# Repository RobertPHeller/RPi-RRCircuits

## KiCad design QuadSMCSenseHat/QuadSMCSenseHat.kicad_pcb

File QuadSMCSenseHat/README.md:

# QuadSMCSenseHat

Quad Stall Motor w/ Sense Hat for a Raspberry Pi.

* [Order this board from The Country Robot](https://www.thecountryrobot.com/product/quad-stall-motor-control-and-sense-hat-for-rpi-bare-circuit-board-w-doc/)
* [Order this board from PCBWay](https://www.pcbway.com/project/shareproject/Quad_Stall_Motor_Controller_w__point_Sense__hat_.html)

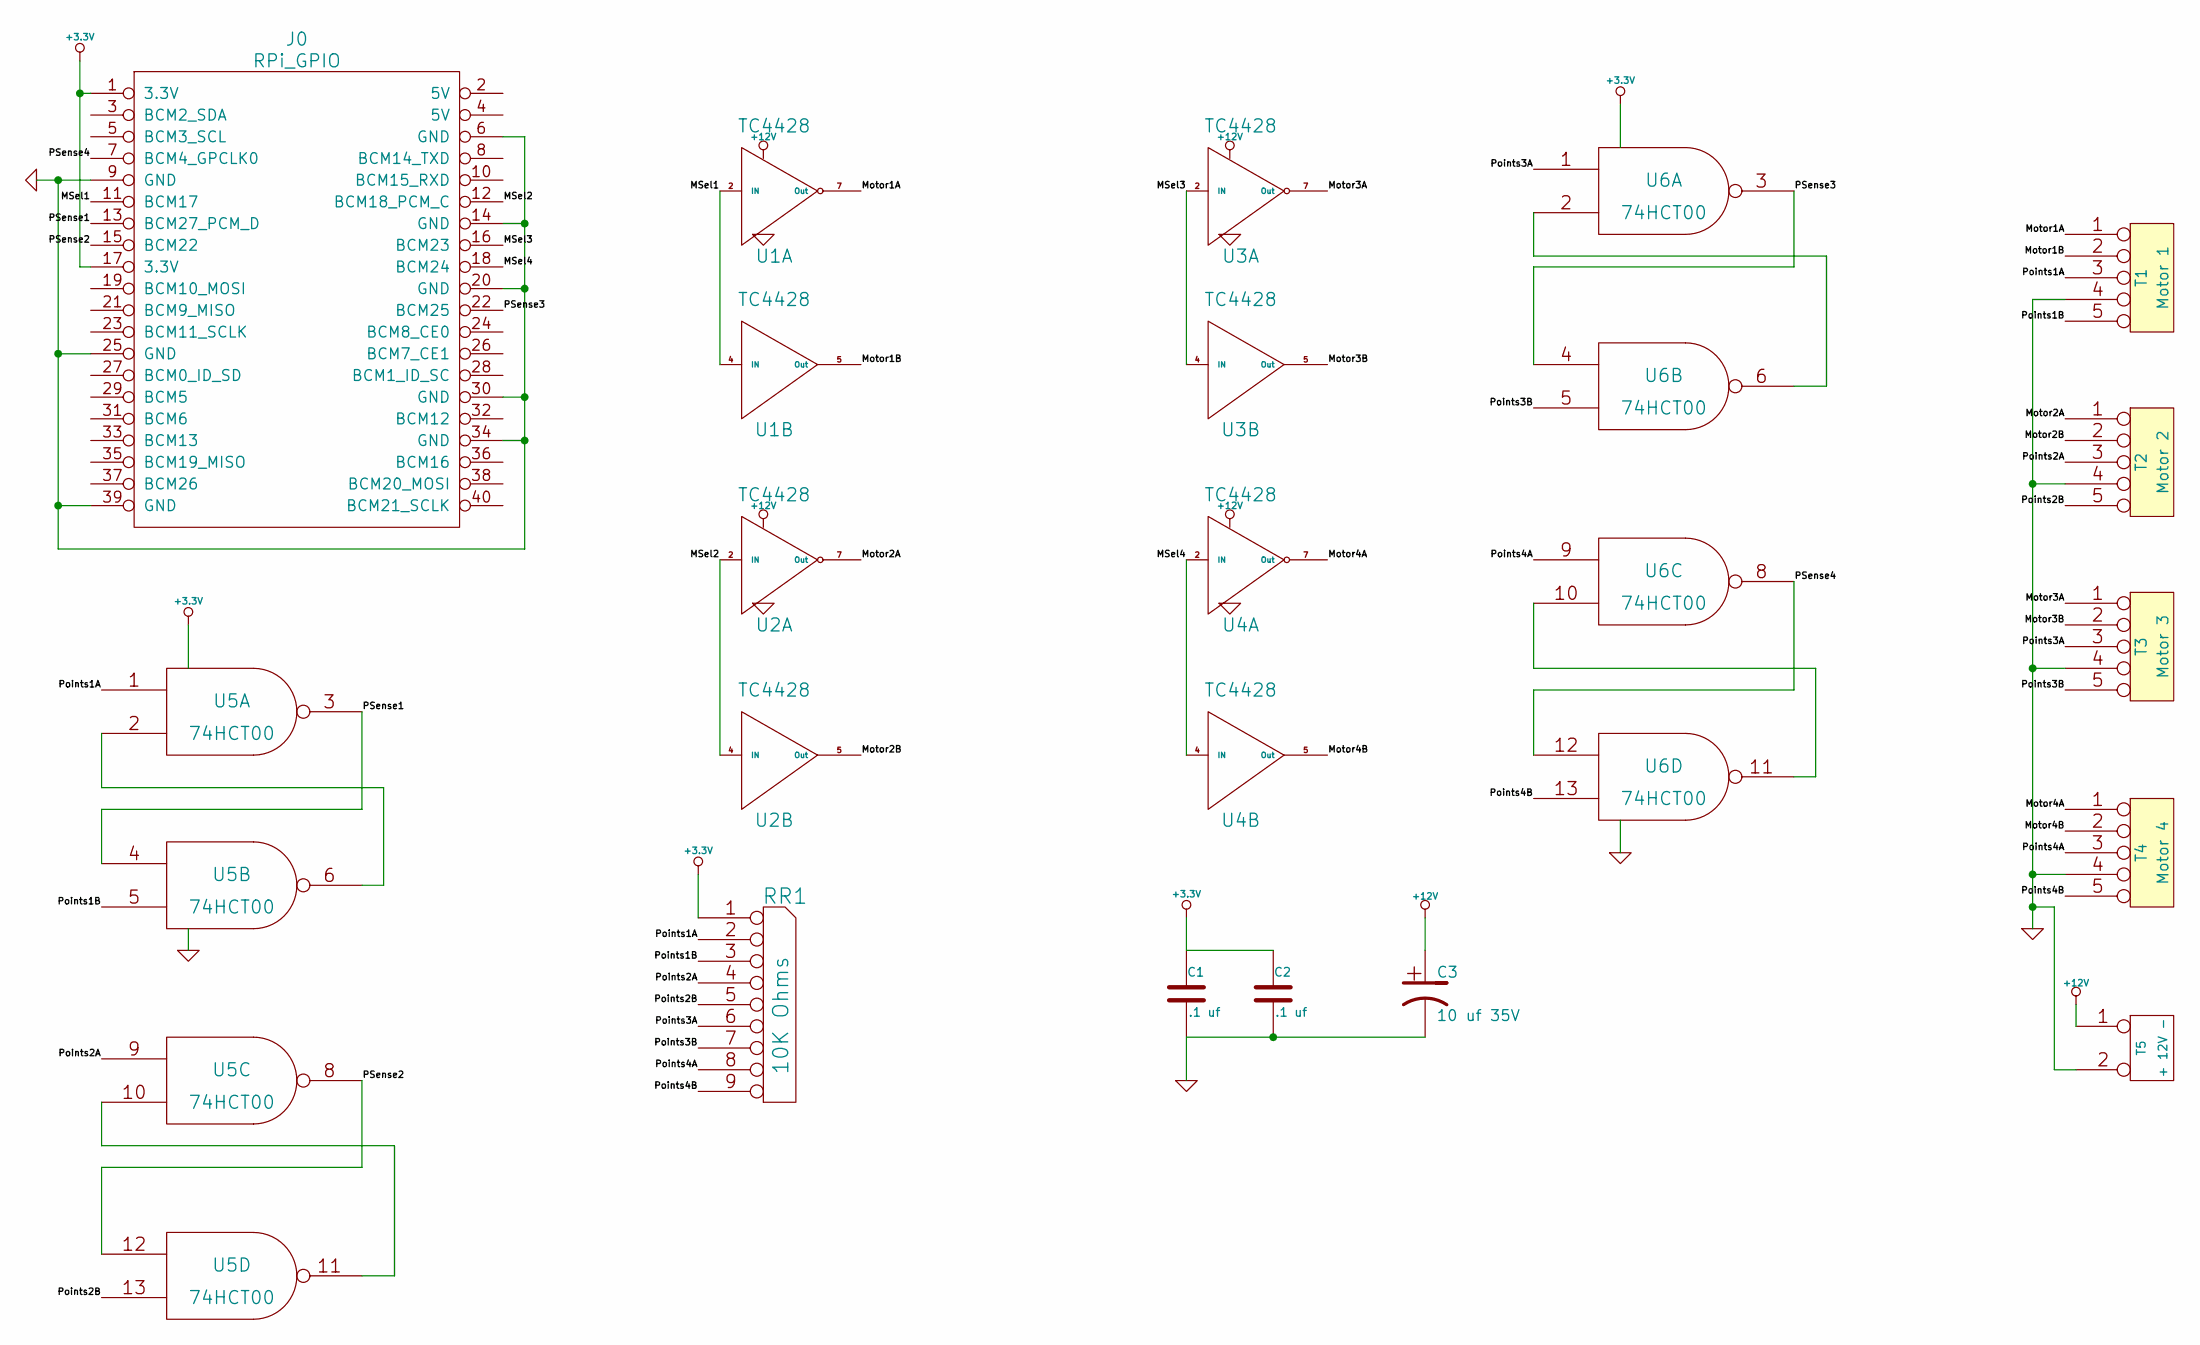
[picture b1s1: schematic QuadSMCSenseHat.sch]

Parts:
C1, C2: .1 uf; Mouser Part Number 581-SR201C104KARTR1
C3: 10 uf 35V; Mouser Part Number 667-ECA-1HM100I
J0: RPi_GPIO; Pin_Header_Straight_2x20; Mouser Part Number 855-M20-6102045
RR1: 10K Ohms; Mouser Part Number 652-4609X-1LF-10K
T1: Motor 1; Mouser Part Number 651-1725685
T2: Motor 2; Mouser Part Number 651-1725685
T3: Motor 3; Mouser Part Number 651-1725685
T4: Motor 4; Mouser Part Number 651-1725685
T5: + 12V -; Mouser Part Number 651-1725656
U1, U2, U3, U4: TC4428; Mouser Part Number 579-TC4428VPA
U5, U6: 74HCT00; Mouser Part Number 595-SN74AHC00N

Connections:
+3.3V: C1.1, C2.1, J0.1 (3.3V), J0.17 (3.3V), RR1.1 (COM), U5.14 (VCC), U6.14 (VCC)
+12V: C3.1, T5.1, U1.6 (Vdd), U2.6 (Vdd), U3.6 (Vdd), U4.6 (Vdd)
/MSel1: J0.11 (BCM17), U1.2 (IN), U1.4 (IN)
/MSel2: J0.12 (BCM18_PCM_C), U2.2 (IN), U2.4 (IN)
/MSel3: J0.16 (BCM23), U3.2 (IN), U3.4 (IN)
/MSel4: J0.18 (BCM24), U4.2 (IN), U4.4 (IN)
/Motor1A: T1.1, U1.7 (Out)
/Motor1B: T1.2, U1.5 (Out)
/Motor2A: T2.1, U2.7 (Out)
/Motor2B: T2.2, U2.5 (Out)
/Motor3A: T3.1, U3.7 (Out)
/Motor3B: T3.2, U3.5 (Out)
/Motor4A: T4.1, U4.7 (Out)
/Motor4B: T4.2, U4.5 (Out)
/PSense1: J0.13 (BCM27_PCM_D), U5.3, U5.4
/PSense2: J0.15 (BCM22), U5.8, U5.12
/PSense3: J0.22 (BCM25), U6.3, U6.4
/PSense4: J0.7 (BCM4_GPCLK0), U6.8, U6.12
/Points1A: RR1.2, T1.3, U5.1
/Points1B: RR1.3, T1.5, U5.5
/Points2A: RR1.4, T2.3, U5.9
/Points2B: RR1.5, T2.5, U5.13
/Points3A: RR1.6, T3.3, U6.1
/Points3B: RR1.7, T3.5, U6.5
/Points4A: RR1.8, T4.3, U6.9
/Points4B: RR1.9, T4.5, U6.13
GND: C1.2, C2.2, C3.2, J0.6 (GND), J0.9 (GND), J0.14 (GND), J0.20 (GND), J0.25 (GND), J0.30 (GND), J0.34 (GND), J0.39 (GND), T1.4, T2.4, T3.4, T4.4, T5.2 (PM), U1.3 (GND), U2.3 (GND), U3.3 (GND), U4.3 (GND), U5.7 (GND), U6.7 (GND)
unnamed: U5.10, U5.11
unnamed: U5.2, U5.6
unnamed: U6.10, U6.11
unnamed: U6.2, U6.6

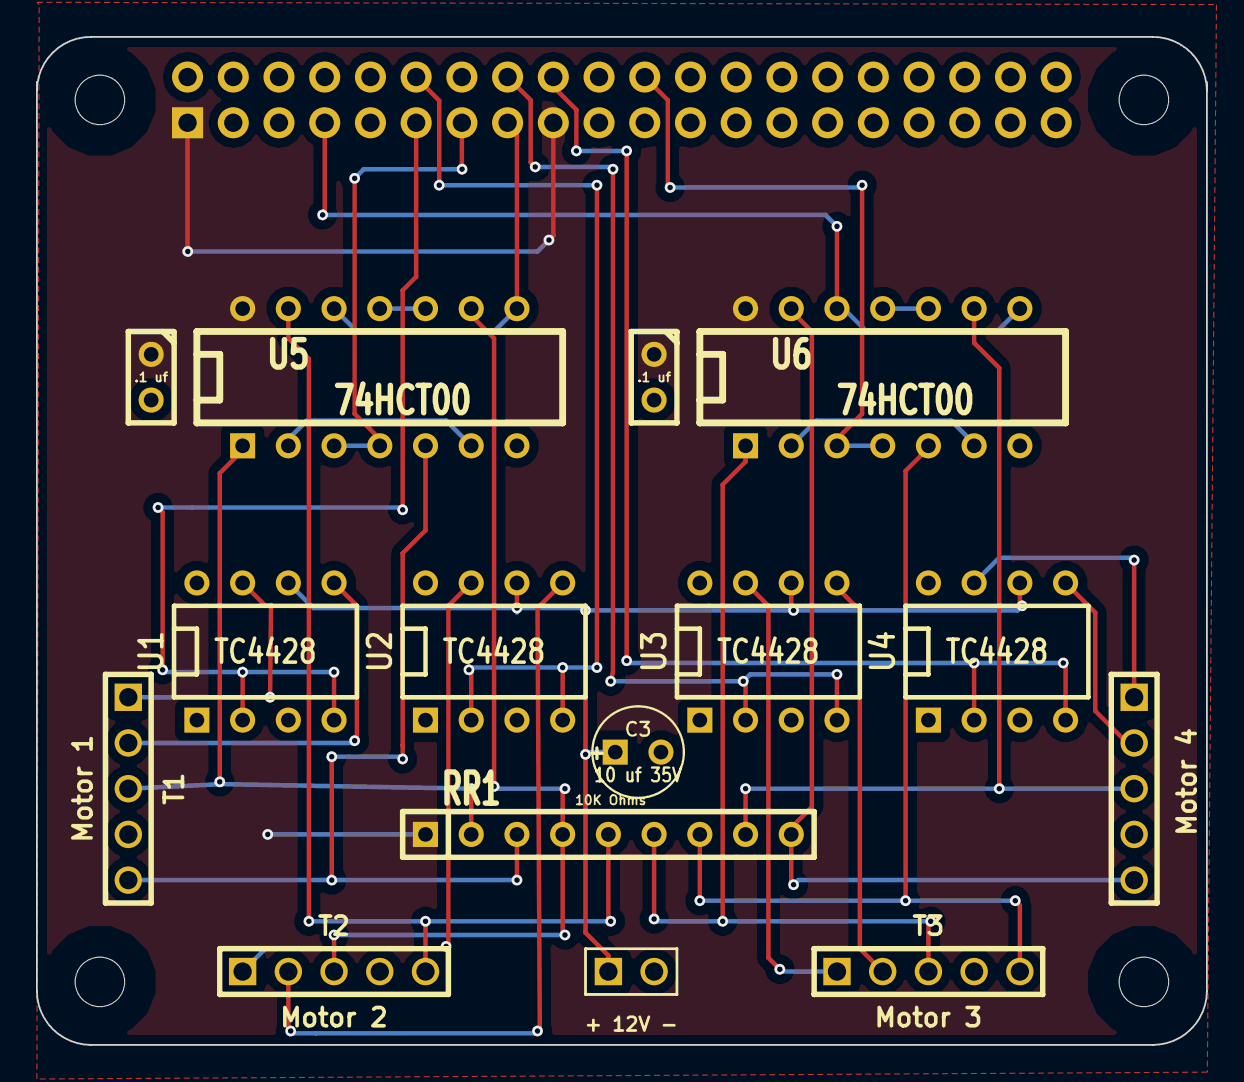
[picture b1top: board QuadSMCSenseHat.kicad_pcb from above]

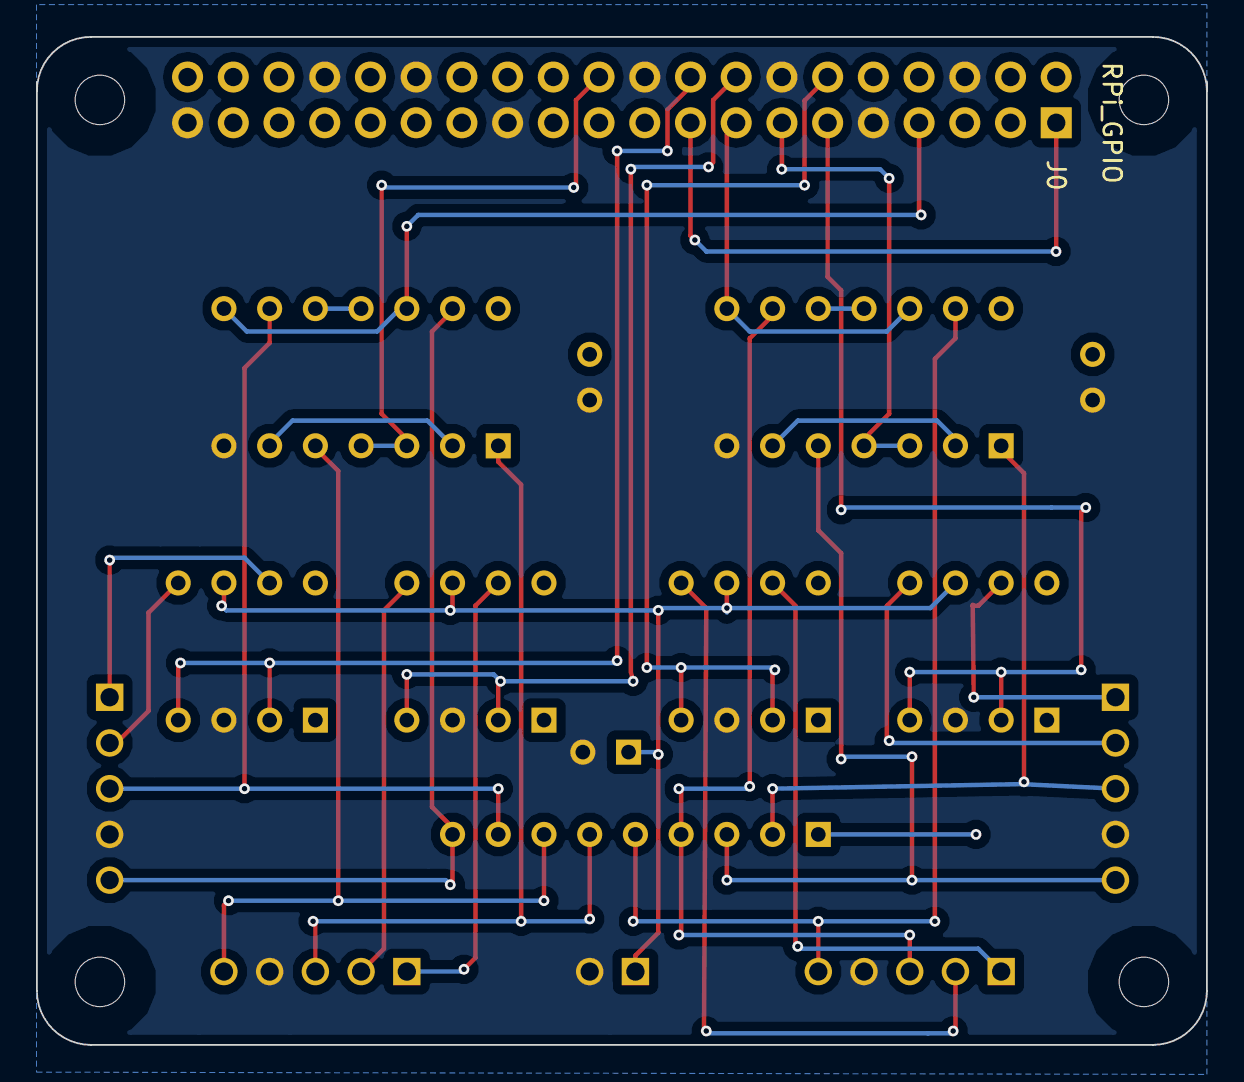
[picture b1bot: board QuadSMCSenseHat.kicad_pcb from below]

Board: 2 copper layers, 65.0 x 56.0 mm, 20 parts (5 on the bottom side), 31 nets.

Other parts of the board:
H1, H2, H3, H4: RPi_Hat_Mounting_Hole

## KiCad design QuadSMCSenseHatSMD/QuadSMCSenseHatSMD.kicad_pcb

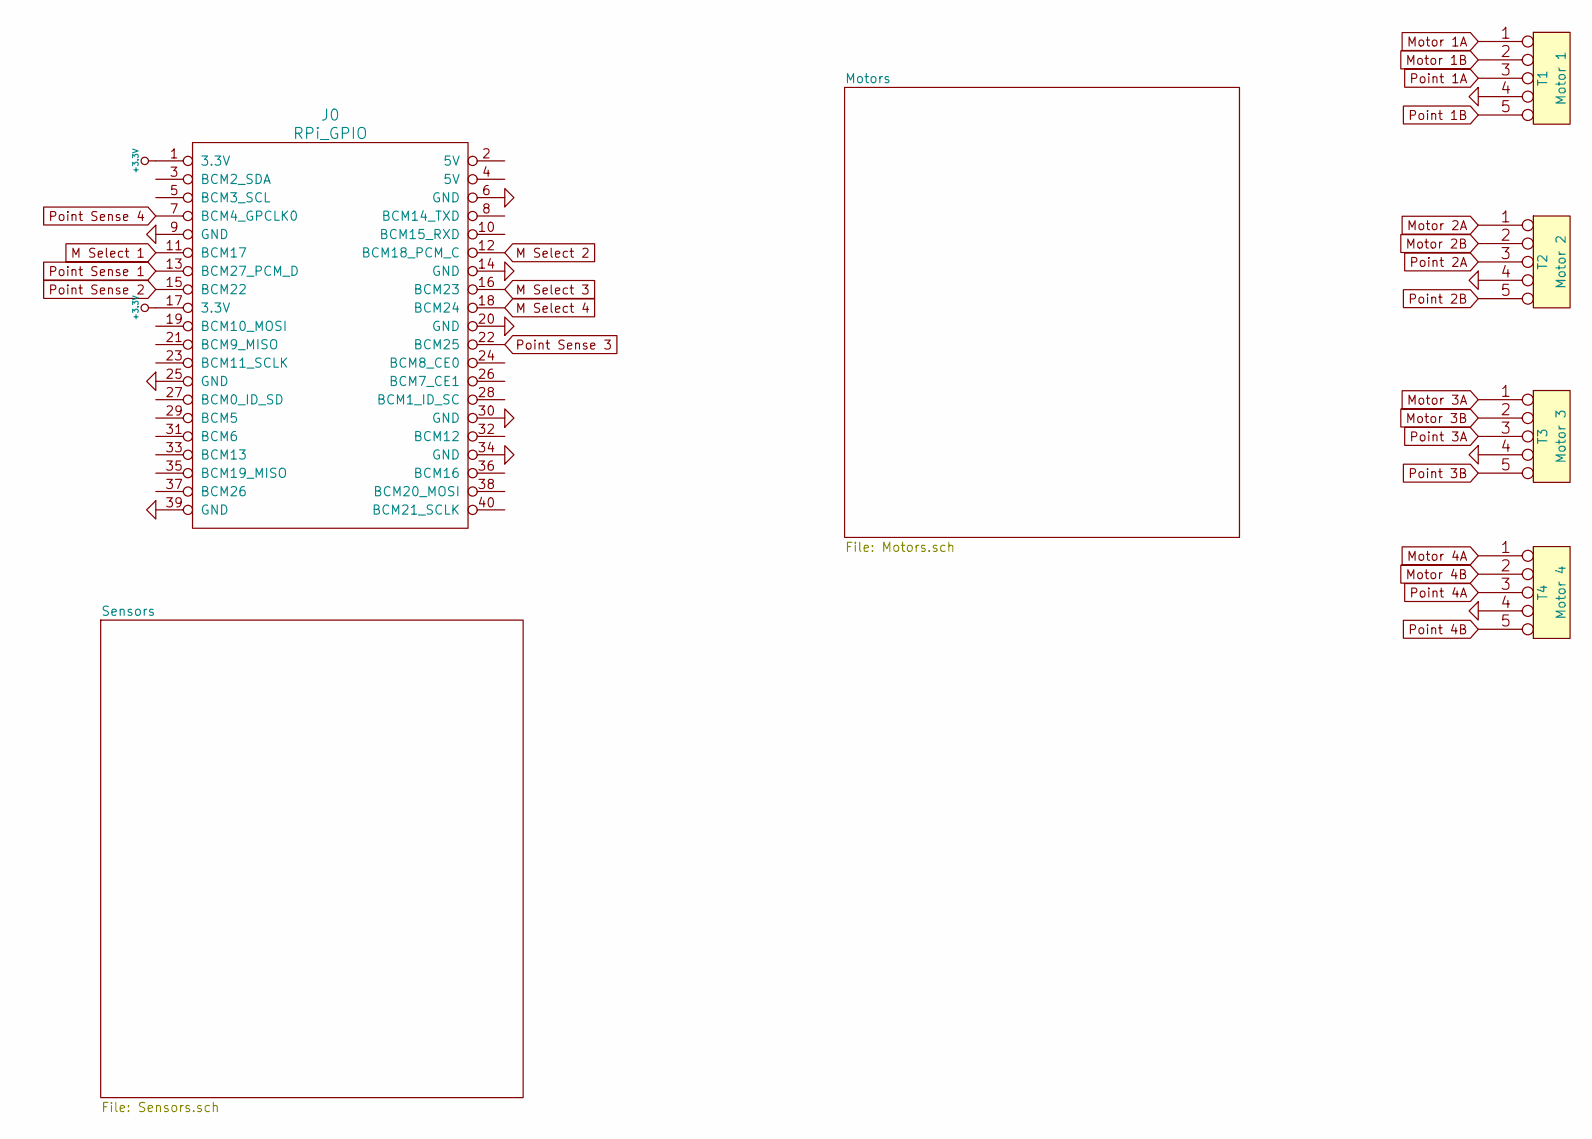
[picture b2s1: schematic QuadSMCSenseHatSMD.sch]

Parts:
J0: RPi_GPIO; Pin_Header_Straight_2x20
T1: Motor 1
T2: Motor 2
T3: Motor 3
T4: Motor 4

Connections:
+3.3V: J0.1 (3.3V), J0.17 (3.3V); also elsewhere on the board
GND: J0.6 (GND), J0.9 (GND), J0.14 (GND), J0.20 (GND), J0.25 (GND), J0.30 (GND), J0.34 (GND), J0.39 (GND), T1.4, T2.4, T3.4, T4.4; also elsewhere on the board
M Select 1: J0.11 (BCM17); also elsewhere on the board
M Select 2: J0.12 (BCM18_PCM_C); also elsewhere on the board
M Select 3: J0.16 (BCM23); also elsewhere on the board
M Select 4: J0.18 (BCM24); also elsewhere on the board
Motor 1A: T1.1; also elsewhere on the board
Motor 1B: T1.2; also elsewhere on the board
Motor 2A: T2.1; also elsewhere on the board
Motor 2B: T2.2; also elsewhere on the board
Motor 3A: T3.1; also elsewhere on the board
Motor 3B: T3.2; also elsewhere on the board
Motor 4A: T4.1; also elsewhere on the board
Motor 4B: T4.2; also elsewhere on the board
Point 1A: T1.3; also elsewhere on the board
Point 1B: T1.5; also elsewhere on the board
Point 2A: T2.3; also elsewhere on the board
Point 2B: T2.5; also elsewhere on the board
Point 3A: T3.3; also elsewhere on the board
Point 3B: T3.5; also elsewhere on the board
Point 4A: T4.3; also elsewhere on the board
Point 4B: T4.5; also elsewhere on the board
Point Sense 1: J0.13 (BCM27_PCM_D); also elsewhere on the board
Point Sense 2: J0.15 (BCM22); also elsewhere on the board
Point Sense 3: J0.22 (BCM25); also elsewhere on the board
Point Sense 4: J0.7 (BCM4_GPCLK0); also elsewhere on the board

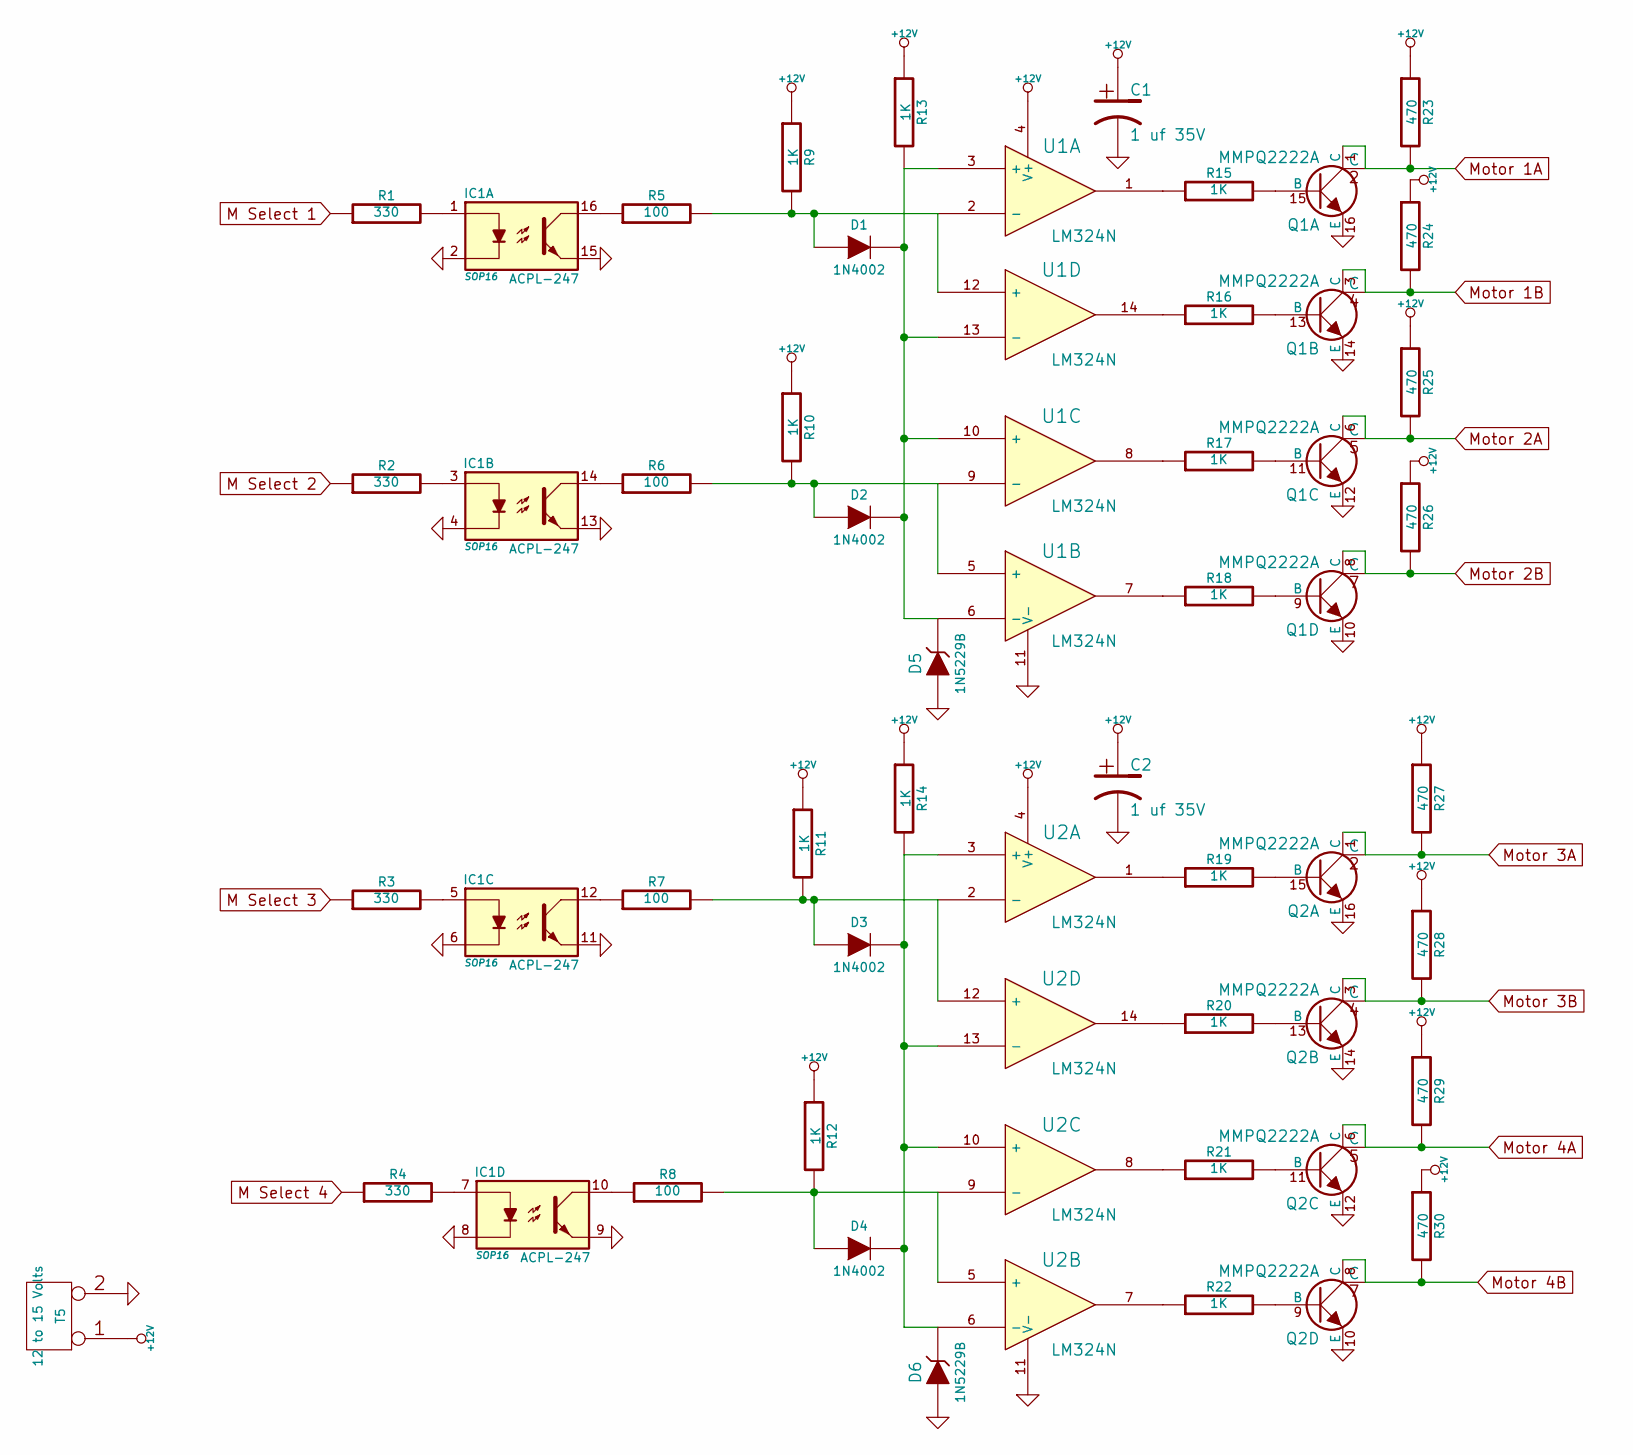
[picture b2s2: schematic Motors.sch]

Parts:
C1, C2: 1 uf 35V; c_elec_3x5.3
D1, D2, D3, D4: 1N4002; DO-214AA(SMB)
D5: 1N5229B; DO-214AC(SMA)
D6: 1N5229B; DO214AC(SMA)
IC1: ACPL-247; SOP16
Q1, Q2: MMPQ2222A
R1: 330; SM0805
R2, R3, R4: 330
R5, R6, R7, R8: 100
R9, R10, R11, R12, R13, R14, R15, R16, R17, R18, R19, R20, R21, R22: 1K
R23, R24, R25, R26, R27, R28, R29, R30: 470
T5: 12 to 15 Volts
U1, U2: LM324N

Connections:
+12V: C1.1, C2.1, R9.1, R10.1, R11.1, R12.1, R13.1, R14.1, R23.1, R24.1, R25.1, R26.1, R27.1, R28.1, R29.1, R30.1, T5.1, U1.4 (V+), U2.4 (V+)
GND: C1.2, C2.2, D5.1 (A), D6.1 (A), IC1.2, IC1.4, IC1.6, IC1.8, IC1.9, IC1.11, IC1.13, IC1.15, Q1.10 (E), Q1.12 (E), Q1.14 (E), Q1.16 (E), Q2.10 (E), Q2.12 (E), Q2.14 (E), Q2.16 (E), T5.2 (PM), U1.11 (V-), U2.11 (V-); also elsewhere on the board
M Select 1: R1.1; also elsewhere on the board
M Select 2: R2.1; also elsewhere on the board
M Select 3: R3.1; also elsewhere on the board
M Select 4: R4.1; also elsewhere on the board
Motor 1A: Q1.1 (C), Q1.2 (C), R23.2; also elsewhere on the board
Motor 1B: Q1.3 (C), Q1.4 (C), R24.2; also elsewhere on the board
Motor 2A: Q1.5 (C), Q1.6 (C), R25.2; also elsewhere on the board
Motor 2B: Q1.7 (C), Q1.8 (C), R26.2; also elsewhere on the board
Motor 3A: Q2.1 (C), Q2.2 (C), R27.2; also elsewhere on the board
Motor 3B: Q2.3 (C), Q2.4 (C), R28.2; also elsewhere on the board
Motor 4A: Q2.5 (C), Q2.6 (C), R29.2; also elsewhere on the board
Motor 4B: Q2.7 (C), Q2.8 (C), R30.2; also elsewhere on the board
unnamed: Q2.13 (B), R20.2
unnamed: Q2.15 (B), R19.2
unnamed: Q1.9 (B), R18.2
unnamed: Q1.11 (B), R17.2
unnamed: Q1.13 (B), R16.2
unnamed: Q2.9 (B), R22.2
unnamed: Q2.11 (B), R21.2
unnamed: R15.1, U1.1
unnamed: Q1.15 (B), R15.2
unnamed: R22.1, U2.7
unnamed: R21.1, U2.8
unnamed: R20.1, U2.14
unnamed: R19.1, U2.1
unnamed: R18.1, U1.7
unnamed: R17.1, U1.8
unnamed: R16.1, U1.14
unnamed: IC1.10, R8.1
unnamed: IC1.12, R7.1
unnamed: IC1.14, R6.1
unnamed: IC1.16, R5.1
unnamed: IC1.3, R2.2
unnamed: IC1.1, R1.2
unnamed: IC1.7, R4.2
unnamed: IC1.5, R3.2
unnamed: D4.1 (A), R8.2, R12.2, U2.5 (+), U2.9 (-)
unnamed: D2.1 (A), R6.2, R10.2, U1.5 (+), U1.9 (-)
unnamed: D1.1 (A), R5.2, R9.2, U1.2 (-), U1.12 (+)
unnamed: D3.2 (K), D4.2 (K), D6.2 (K), R14.2, U2.3 (+), U2.6 (-), U2.10 (+), U2.13 (-)
unnamed: D1.2 (K), D2.2 (K), D5.2 (K), R13.2, U1.3 (+), U1.6 (-), U1.10 (+), U1.13 (-)
unnamed: D3.1 (A), R7.2, R11.2, U2.2 (-), U2.12 (+)

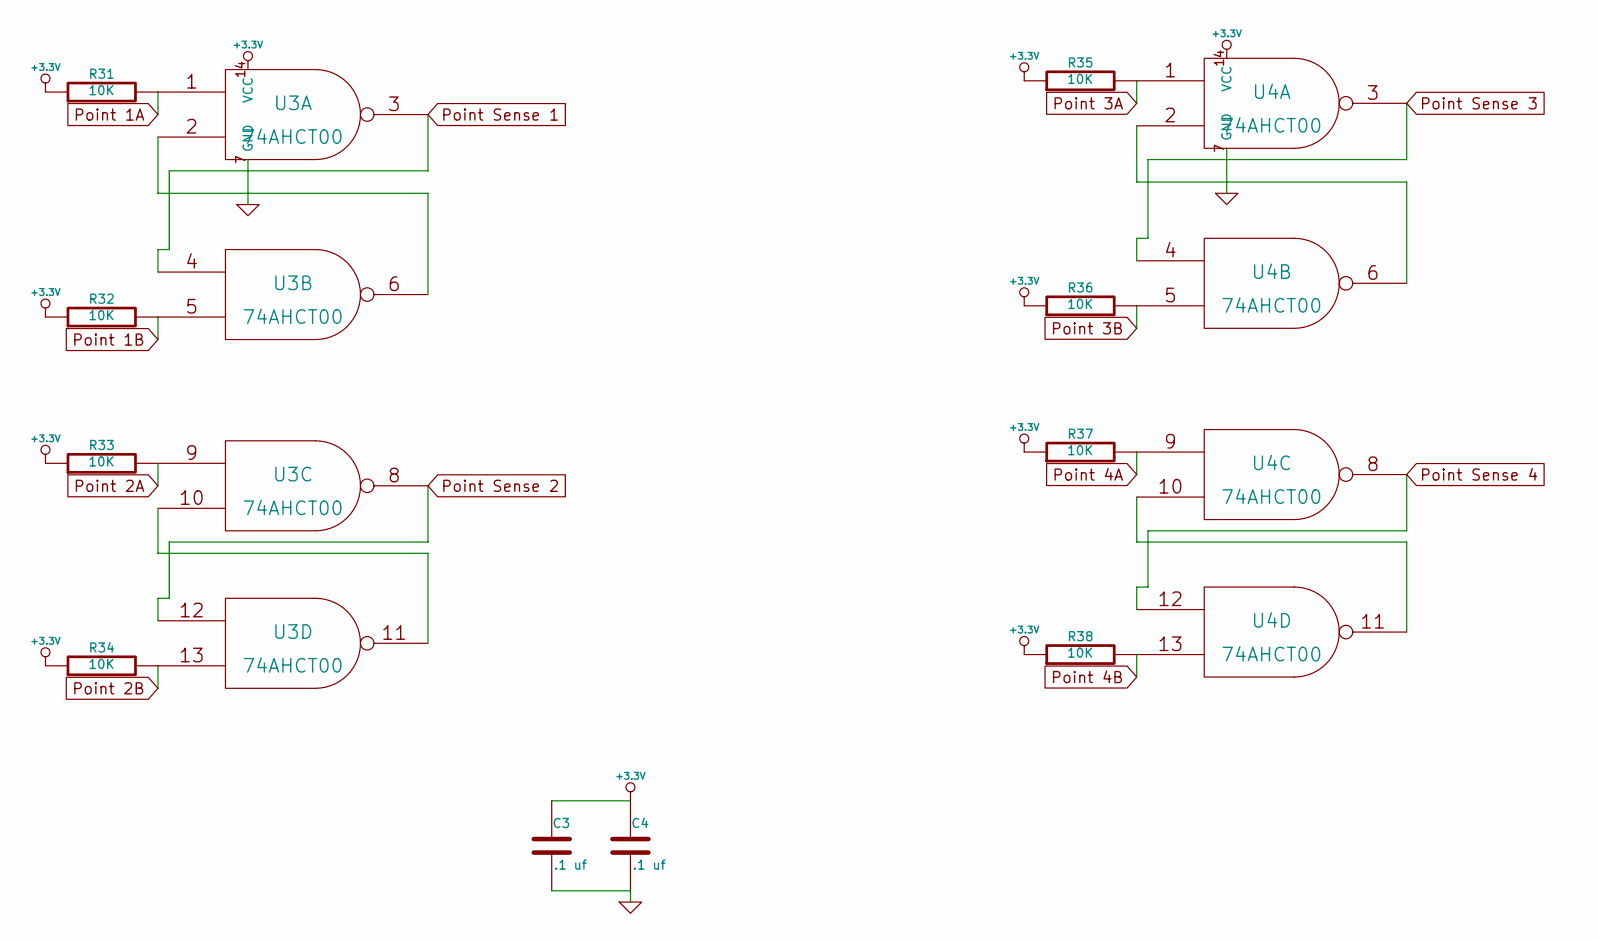
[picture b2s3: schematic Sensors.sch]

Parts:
C3, C4: .1 uf
R31, R32, R33, R34, R35, R36, R37, R38: 10K
U3, U4: 74AHCT00

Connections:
+3.3V: C3.1, C4.1, R31.1, R32.1, R33.1, R34.1, R35.1, R36.1, R37.1, R38.1, U3.14 (VCC), U4.14 (VCC); also elsewhere on the board
GND: C3.2, C4.2, U3.7 (GND), U4.7 (GND); also elsewhere on the board
unnamed: U4.2, U4.6
unnamed: U3.10, U3.11
unnamed: U3.2, U3.6
unnamed: U4.10, U4.11
Point 1A: R31.2, U3.1; also elsewhere on the board
Point 1B: R32.2, U3.5; also elsewhere on the board
Point 2A: R33.2, U3.9; also elsewhere on the board
Point 2B: R34.2, U3.13; also elsewhere on the board
Point 3A: R35.2, U4.1; also elsewhere on the board
Point 3B: R36.2, U4.5; also elsewhere on the board
Point 4A: R37.2, U4.9; also elsewhere on the board
Point 4B: R38.2, U4.13; also elsewhere on the board
Point Sense 1: U3.3, U3.4; also elsewhere on the board
Point Sense 2: U3.8, U3.12; also elsewhere on the board
Point Sense 3: U4.3, U4.4; also elsewhere on the board
Point Sense 4: U4.8, U4.12; also elsewhere on the board

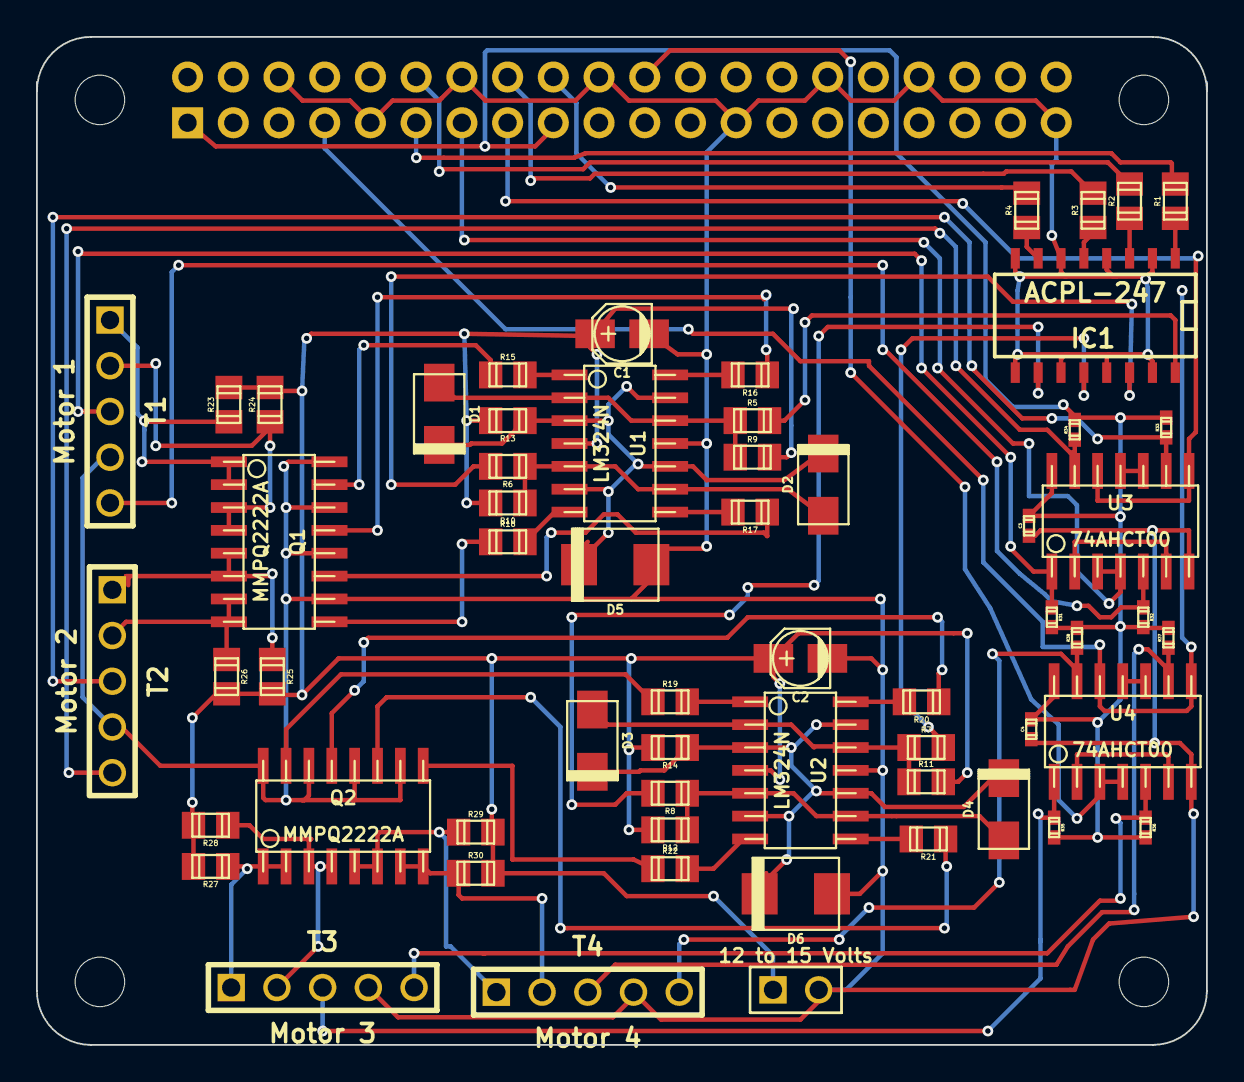
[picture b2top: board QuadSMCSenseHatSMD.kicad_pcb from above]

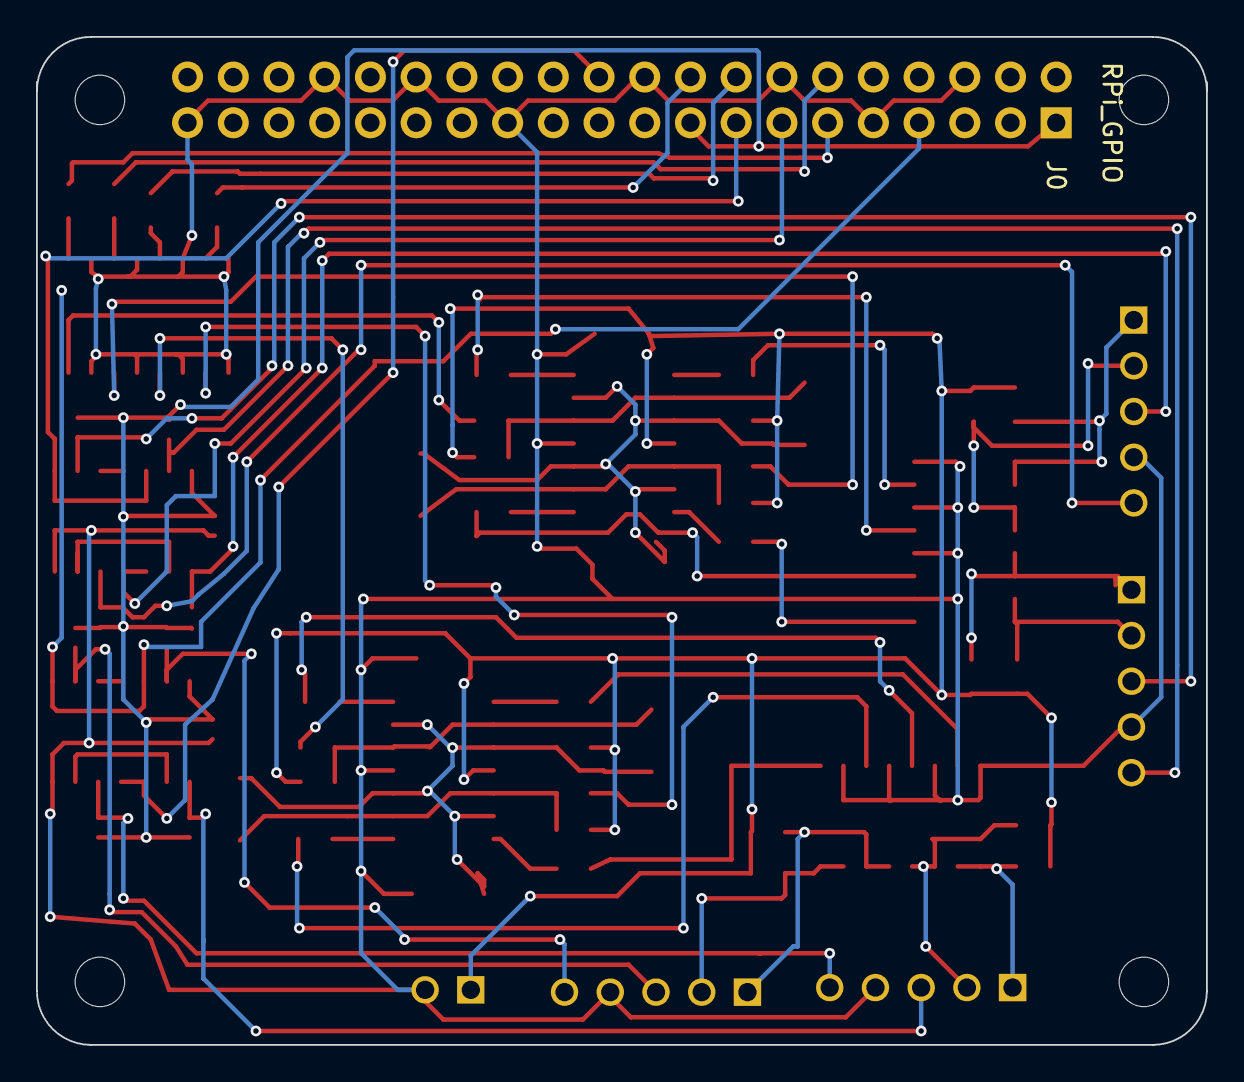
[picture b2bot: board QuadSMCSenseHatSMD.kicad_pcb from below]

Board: 2 copper layers, 65.0 x 56.0 mm, 65 parts (5 on the bottom side), 61 nets.

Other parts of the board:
H1, H2, H3, H4: RPi_Hat_Mounting_Hole

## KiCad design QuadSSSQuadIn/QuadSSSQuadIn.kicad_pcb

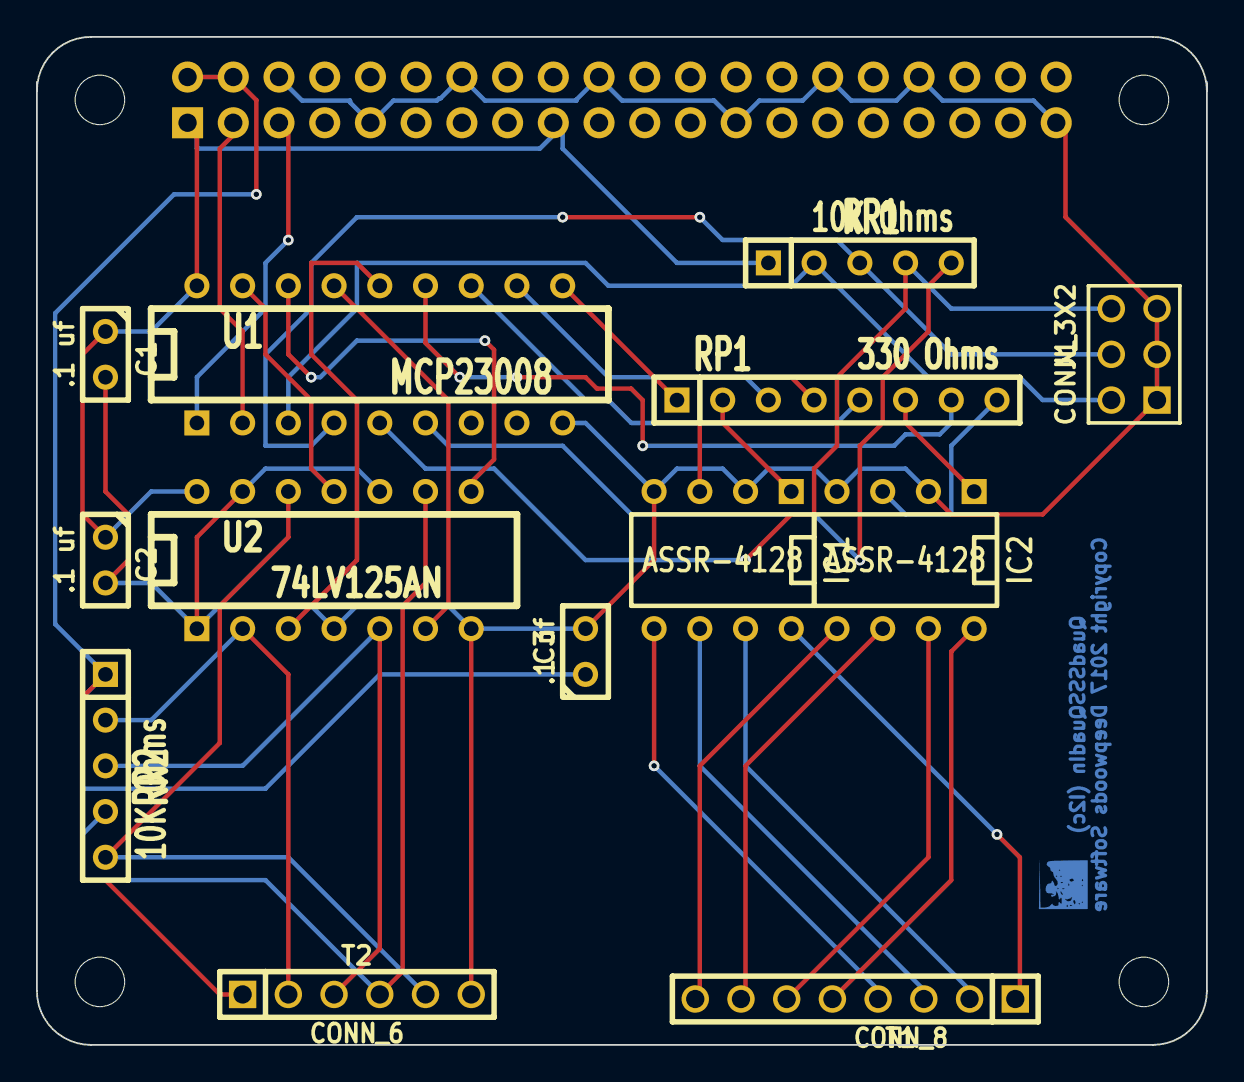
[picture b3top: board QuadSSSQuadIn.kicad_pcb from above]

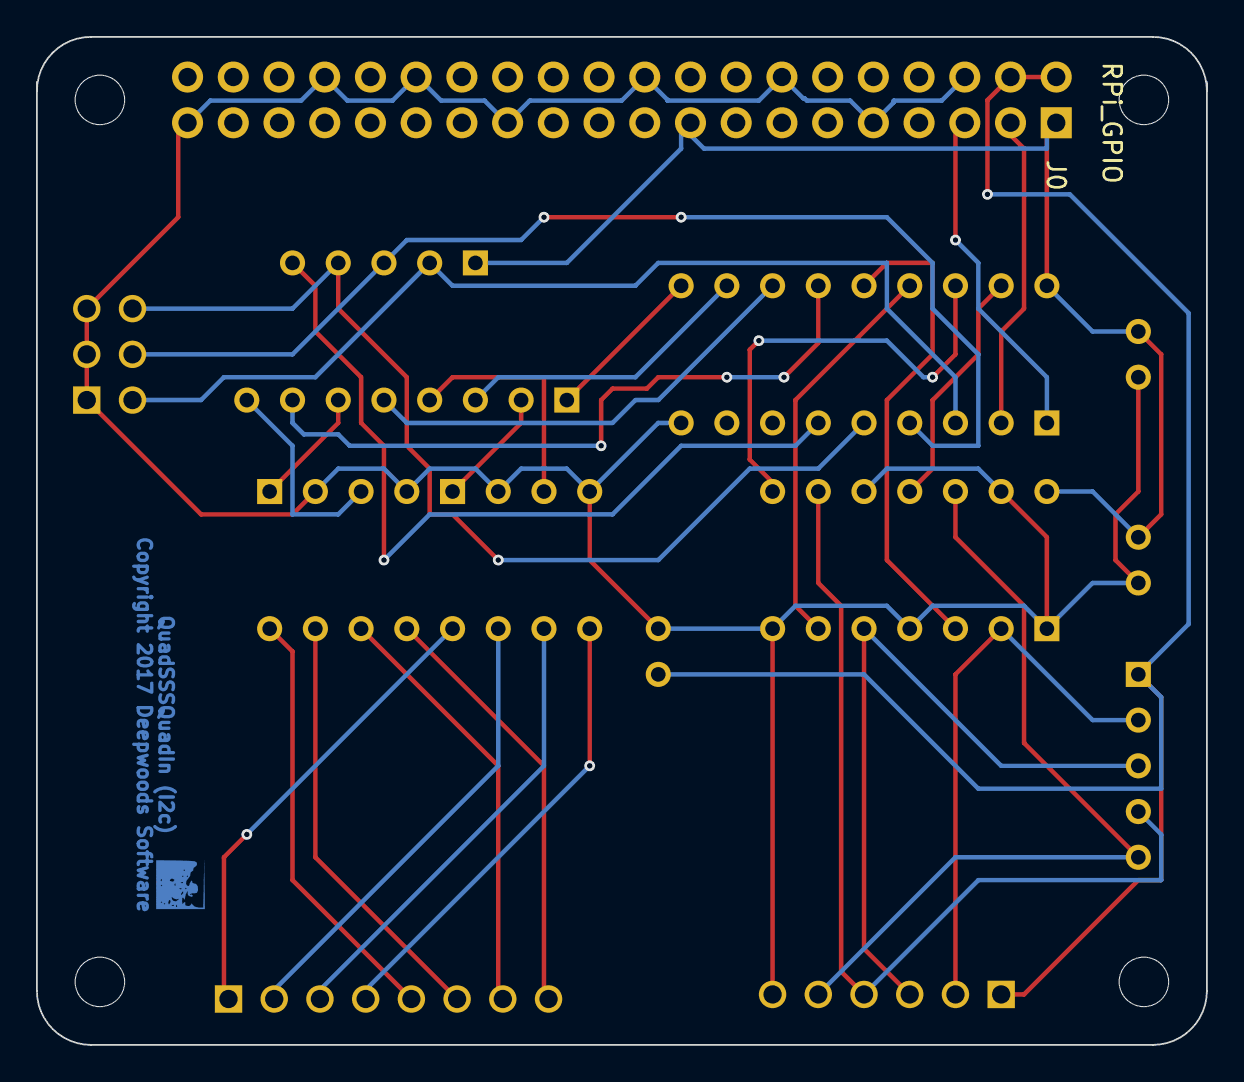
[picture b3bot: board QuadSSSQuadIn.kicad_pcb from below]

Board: 2 copper layers, 65.0 x 56.0 mm, 18 parts (5 on the bottom side), 31 nets.

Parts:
C1, C2, C3: .1 uf; C1
H1, H2, H3, H4: RPi_Hat_Mounting_Hole
IC1, IC2: ASSR-4128; DIP-8__300
J0: RPi_GPIO; Pin_Header_Straight_2x20
J1: CONN_3X2; pin_array_3x2
RP1: 330 Ohms; SIL-8
RR1, RR2: 10K Ohms; SIL-5
T1: CONN_8; PIN_ARRAY-6X1
T2: CONN_6; PIN_ARRAY-6X1
U1: MCP23008; DIP-18__300
U2: 74LV125AN; DIP-14__300

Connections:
+5V: C3.1, J0.2, J0.4, RR2.1, T2.1
GND: C1.2, C2.2, C3.2, IC1.2, IC1.4, IC2.2, IC2.4, J0.6, J0.9, J0.14, J0.20, J0.25, J0.30, J0.34, J0.39, J1.1, J1.3, J1.5, T2.6, U1.9, U2.1, U2.4, U2.7, U2.10, U2.13
unnamed: RP1.7, U1.13
unnamed: RP1.5, U1.12
unnamed: RP1.3, U1.11
unnamed: RP1.1, U1.10
unnamed: RR2.2, T2.2, U2.2
unnamed: IC2.3, RP1.8
unnamed: IC2.7, T1.6
unnamed: IC2.8, T1.5
unnamed: IC1.5, T1.4
unnamed: IC1.6, T1.3
unnamed: IC1.7, T1.2
unnamed: IC1.8, T1.1
unnamed: RR2.3, T2.3, U2.5
unnamed: RR2.5, T2.5, U2.12
unnamed: RR2.4, T2.4, U2.9
unnamed: U1.17, U2.11
unnamed: U1.16, U2.8
unnamed: U1.15, U2.6
unnamed: U1.14, U2.3
unnamed: RR1.5, U1.6
unnamed: J0.5, U1.1
unnamed: J0.3, U1.2
unnamed: IC1.3, RP1.4
unnamed: IC1.1, RP1.2
unnamed: J1.6, RR1.4, U1.5
unnamed: J1.4, RR1.3, U1.4
unnamed: IC2.1, RP1.6
unnamed: J1.2, RR1.2, U1.3
VDD: C1.1, C2.1, J0.1, J0.17, RR1.1, U1.18, U2.14

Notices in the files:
QuadSSSQuadIn/QuadSSSQuadIn.kicad_pcb:
Copyright 2017 Deepwoods Software
QuadSignalDriverCA/QuadSignalDriverCA.kicad_pcb:
(c) Copyright 2017 Deepwoods Software
QuadUncoupler/QuadUncoupler.kicad_pcb:
Copyright 2016 Deepwoods Software
